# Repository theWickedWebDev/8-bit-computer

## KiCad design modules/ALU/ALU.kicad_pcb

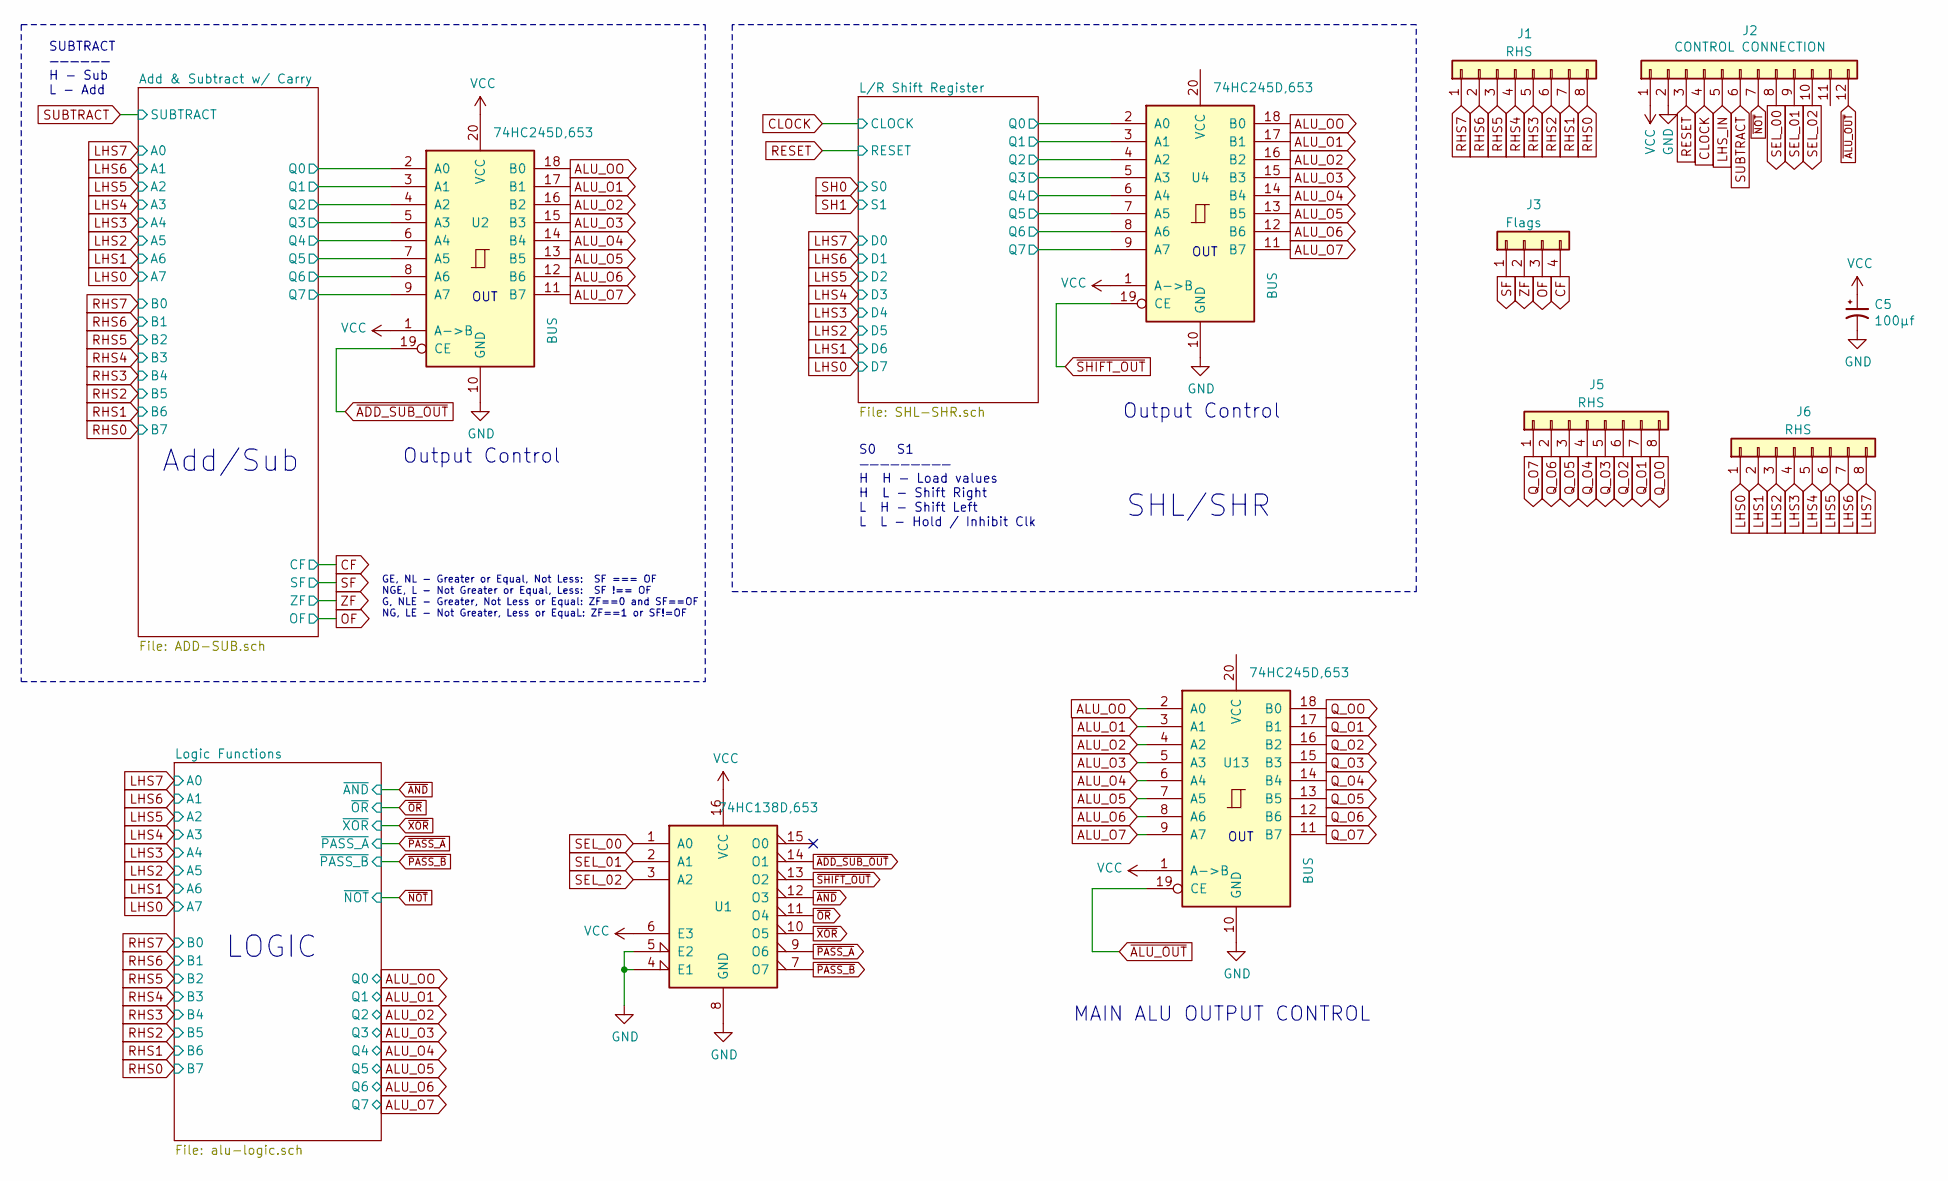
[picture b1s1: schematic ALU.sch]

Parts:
C5: SMD-ECAP-5x5.8; CP_Elec_5x5.8; JLCPCB C140924
J1, J5, J6: Conn_01x08; PinHeader_1x08_P2.54mm_Vertical
J2: Conn_01x12; PinHeader_1x12_P2.54mm_Vertical
J3: Conn_01x04; PinHeader_1x04_P2.54mm_Vertical
U1: 74HC138D,653; SOIC-16_3.9x9.9mm_P1.27mm
U2, U4, U13: 74HC245D,653; SOIC-20W_7.5x12.8mm_P1.27mm

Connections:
/Add & Subtract w/ Carry/Q0: U2.2 (A0); also elsewhere on the board
/Add & Subtract w/ Carry/Q1: U2.3 (A1); also elsewhere on the board
/Add & Subtract w/ Carry/Q2: U2.4 (A2); also elsewhere on the board
/Add & Subtract w/ Carry/Q3: U2.5 (A3); also elsewhere on the board
/Add & Subtract w/ Carry/Q4: U2.6 (A4); also elsewhere on the board
/Add & Subtract w/ Carry/Q5: U2.7 (A5); also elsewhere on the board
/Add & Subtract w/ Carry/Q6: U2.8 (A6); also elsewhere on the board
/Add & Subtract w/ Carry/Q7: U2.9 (A7); also elsewhere on the board
/L/R Shift Register/Q0: U4.2 (A0); also elsewhere on the board
/L/R Shift Register/Q1: U4.3 (A1); also elsewhere on the board
/L/R Shift Register/Q2: U4.4 (A2); also elsewhere on the board
/L/R Shift Register/Q3: U4.5 (A3); also elsewhere on the board
/L/R Shift Register/Q4: U4.6 (A4); also elsewhere on the board
/L/R Shift Register/Q5: U4.7 (A5); also elsewhere on the board
/L/R Shift Register/Q6: U4.8 (A6); also elsewhere on the board
/L/R Shift Register/Q7: U4.9 (A7); also elsewhere on the board
ALU_O1: U2.17 (B1), U4.17 (B1), U13.3 (A1); also elsewhere on the board
ALU_O2: U2.16 (B2), U4.16 (B2), U13.4 (A2); also elsewhere on the board
ALU_O3: U2.15 (B3), U4.15 (B3), U13.5 (A3); also elsewhere on the board
ALU_O4: U2.14 (B4), U4.14 (B4), U13.6 (A4); also elsewhere on the board
ALU_O5: U2.13 (B5), U4.13 (B5), U13.7 (A5); also elsewhere on the board
ALU_O6: U2.12 (B6), U4.12 (B6), U13.8 (A6); also elsewhere on the board
ALU_O7: U2.11 (B7), U4.11 (B7), U13.9 (A7); also elsewhere on the board
ALU_OO: U2.18 (B0), U4.18 (B0), U13.2 (A0); also elsewhere on the board
CF: J3.4; also elsewhere on the board
CLOCK: J2.4; also elsewhere on the board
GND: C5.2, J2.2, U1.4 (E1), U1.5 (E2), U1.8 (GND), U2.10 (GND), U4.10 (GND), U13.10 (GND); also elsewhere on the board
LHS0: J6.1; also elsewhere on the board
LHS1: J6.2; also elsewhere on the board
LHS2: J6.3; also elsewhere on the board
LHS3: J6.4; also elsewhere on the board
LHS4: J6.5; also elsewhere on the board
LHS5: J6.6; also elsewhere on the board
LHS6: J6.7; also elsewhere on the board
LHS7: J6.8; also elsewhere on the board
LHS_IN: J2.5
OF: J3.3
Q_O1: J5.7, U13.17 (B1)
Q_O2: J5.6, U13.16 (B2)
Q_O3: J5.5, U13.15 (B3)
Q_O4: J5.4, U13.14 (B4)
Q_O5: J5.3, U13.13 (B5)
Q_O6: J5.2, U13.12 (B6)
Q_O7: J5.1, U13.11 (B7)
Q_OO: J5.8, U13.18 (B0)
RESET: J2.3; also elsewhere on the board
RHS0: J1.8; also elsewhere on the board
RHS1: J1.7; also elsewhere on the board
RHS2: J1.6; also elsewhere on the board
RHS3: J1.5; also elsewhere on the board
RHS4: J1.4; also elsewhere on the board
RHS5: J1.3; also elsewhere on the board
RHS6: J1.2; also elsewhere on the board
RHS7: J1.1; also elsewhere on the board
SEL_00: J2.8, U1.1 (A0)
SEL_01: J2.9, U1.2 (A1)
SEL_02: J2.10, U1.3 (A2)
SF: J3.1; also elsewhere on the board
SUBTRACT: J2.6; also elsewhere on the board
VCC: C5.1, J2.1, U1.6 (E3), U1.16 (VCC), U2.1 (A->B), U2.20 (VCC), U4.1 (A->B), U13.1 (A->B); also elsewhere on the board
ZF: J3.2; also elsewhere on the board
~ADD_SUB_OUT: U1.14 (O1), U2.19 (CE)
~ALU_OUT: J2.12, U13.19 (CE)
~AND: U1.12 (O3); also elsewhere on the board
~NOT: J2.7; also elsewhere on the board
~OR: U1.11 (O4); also elsewhere on the board
~PASS_A: U1.9 (O6); also elsewhere on the board
~PASS_B: U1.7 (O7); also elsewhere on the board
~SHIFT_OUT: U1.13 (O2), U4.19 (CE)
~XOR: U1.10 (O5); also elsewhere on the board

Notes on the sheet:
OUT
Add/Sub
Output Control
S0 S1 ————————— H H - Load values H L - Shift Right L H - Shift Left L L - Hold / Inhibit Clk
SHL/SHR
SUBTRACT —————— H - Sub L - Add
GE, NL - Greater or Equal, Not Less: SF === OF NGE, L - Not Greater or Equal, Less: SF !== OF G, NLE - Greater, Not Less or Equal: ZF==0 and SF==OF NG, LE - Not Greater, Less or EquaL: ZF==1 or SF!=OF
LOGIC
MAIN ALU OUTPUT CONTROL

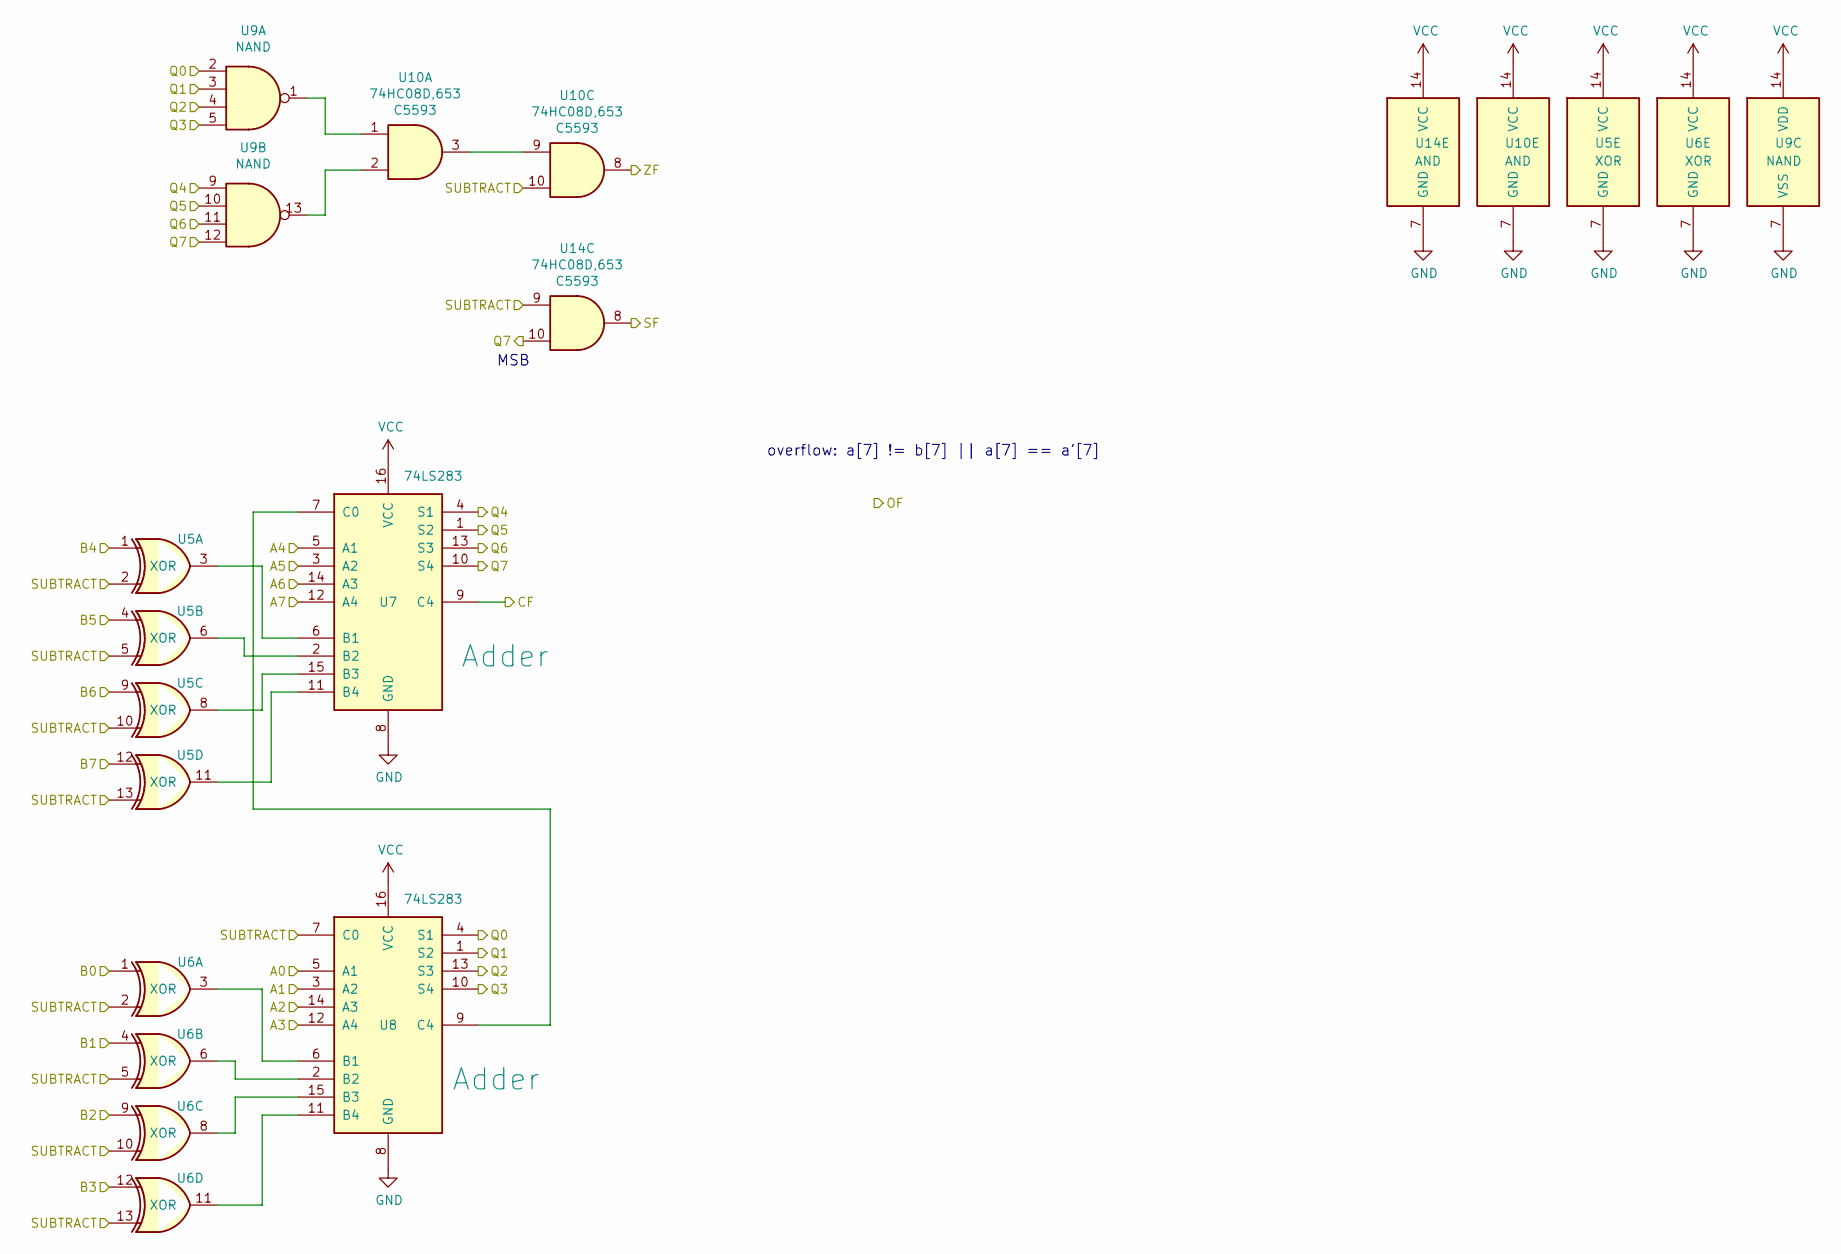
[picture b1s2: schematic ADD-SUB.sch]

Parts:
U5, U6: MM74HC86MX; SOIC-14_3.9x8.7mm_P1.27mm
U7, U8: 74LS283; DIP-16_W7.62mm
U9: CD4012BM; SOIC-14_3.9x8.7mm_P1.27mm
U10, U14: 74HC08D,653; SOIC-14_3.9x8.7mm_P1.27mm

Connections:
/Add & Subtract w/ Carry/Q0: U8.4 (S1), U9.2; also elsewhere on the board
/Add & Subtract w/ Carry/Q1: U8.1 (S2), U9.3; also elsewhere on the board
/Add & Subtract w/ Carry/Q2: U8.13 (S3), U9.4; also elsewhere on the board
/Add & Subtract w/ Carry/Q3: U8.10 (S4), U9.5; also elsewhere on the board
/Add & Subtract w/ Carry/Q4: U7.4 (S1), U9.9; also elsewhere on the board
/Add & Subtract w/ Carry/Q5: U7.1 (S2), U9.10; also elsewhere on the board
/Add & Subtract w/ Carry/Q6: U7.13 (S3), U9.11; also elsewhere on the board
/Add & Subtract w/ Carry/Q7: U7.10 (S4), U9.12, U14.10; also elsewhere on the board
CF: U7.9 (C4); also elsewhere on the board
GND: U5.7 (GND), U6.7 (GND), U7.8 (GND), U8.8 (GND), U9.7 (VSS), U10.7 (GND), U14.7 (GND); also elsewhere on the board
LHS0: U7.12 (A4); also elsewhere on the board
LHS1: U7.14 (A3); also elsewhere on the board
LHS2: U7.3 (A2); also elsewhere on the board
LHS3: U7.5 (A1); also elsewhere on the board
LHS4: U8.12 (A4); also elsewhere on the board
LHS5: U8.14 (A3); also elsewhere on the board
LHS6: U8.3 (A2); also elsewhere on the board
LHS7: U8.5 (A1); also elsewhere on the board
unnamed: U5.3, U7.6 (B1)
unnamed: U5.6, U7.2 (B2)
unnamed: U5.8, U7.15 (B3)
unnamed: U5.11, U7.11 (B4)
unnamed: U6.3, U8.6 (B1)
unnamed: U6.6, U8.2 (B2)
unnamed: U6.8, U8.15 (B3)
unnamed: U6.11, U8.11 (B4)
unnamed: U7.7 (C0), U8.9 (C4)
unnamed: U9.1, U10.1
unnamed: U9.13, U10.2
unnamed: U10.3, U10.9
RHS0: U5.12; also elsewhere on the board
RHS1: U5.9; also elsewhere on the board
RHS2: U5.4; also elsewhere on the board
RHS3: U5.1; also elsewhere on the board
RHS4: U6.12; also elsewhere on the board
RHS5: U6.9; also elsewhere on the board
RHS6: U6.4; also elsewhere on the board
RHS7: U6.1; also elsewhere on the board
SF: U14.8; also elsewhere on the board
SUBTRACT: U5.2, U5.5, U5.10, U5.13, U6.2, U6.5, U6.10, U6.13, U8.7 (C0), U10.10, U14.9; also elsewhere on the board
VCC: U5.14 (VCC), U6.14 (VCC), U7.16 (VCC), U8.16 (VCC), U9.14 (VDD), U10.14 (VCC), U14.14 (VCC); also elsewhere on the board
ZF: U10.8; also elsewhere on the board

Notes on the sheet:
MSB
overflow: a[7] != b[7] || a[7] == a'[7]

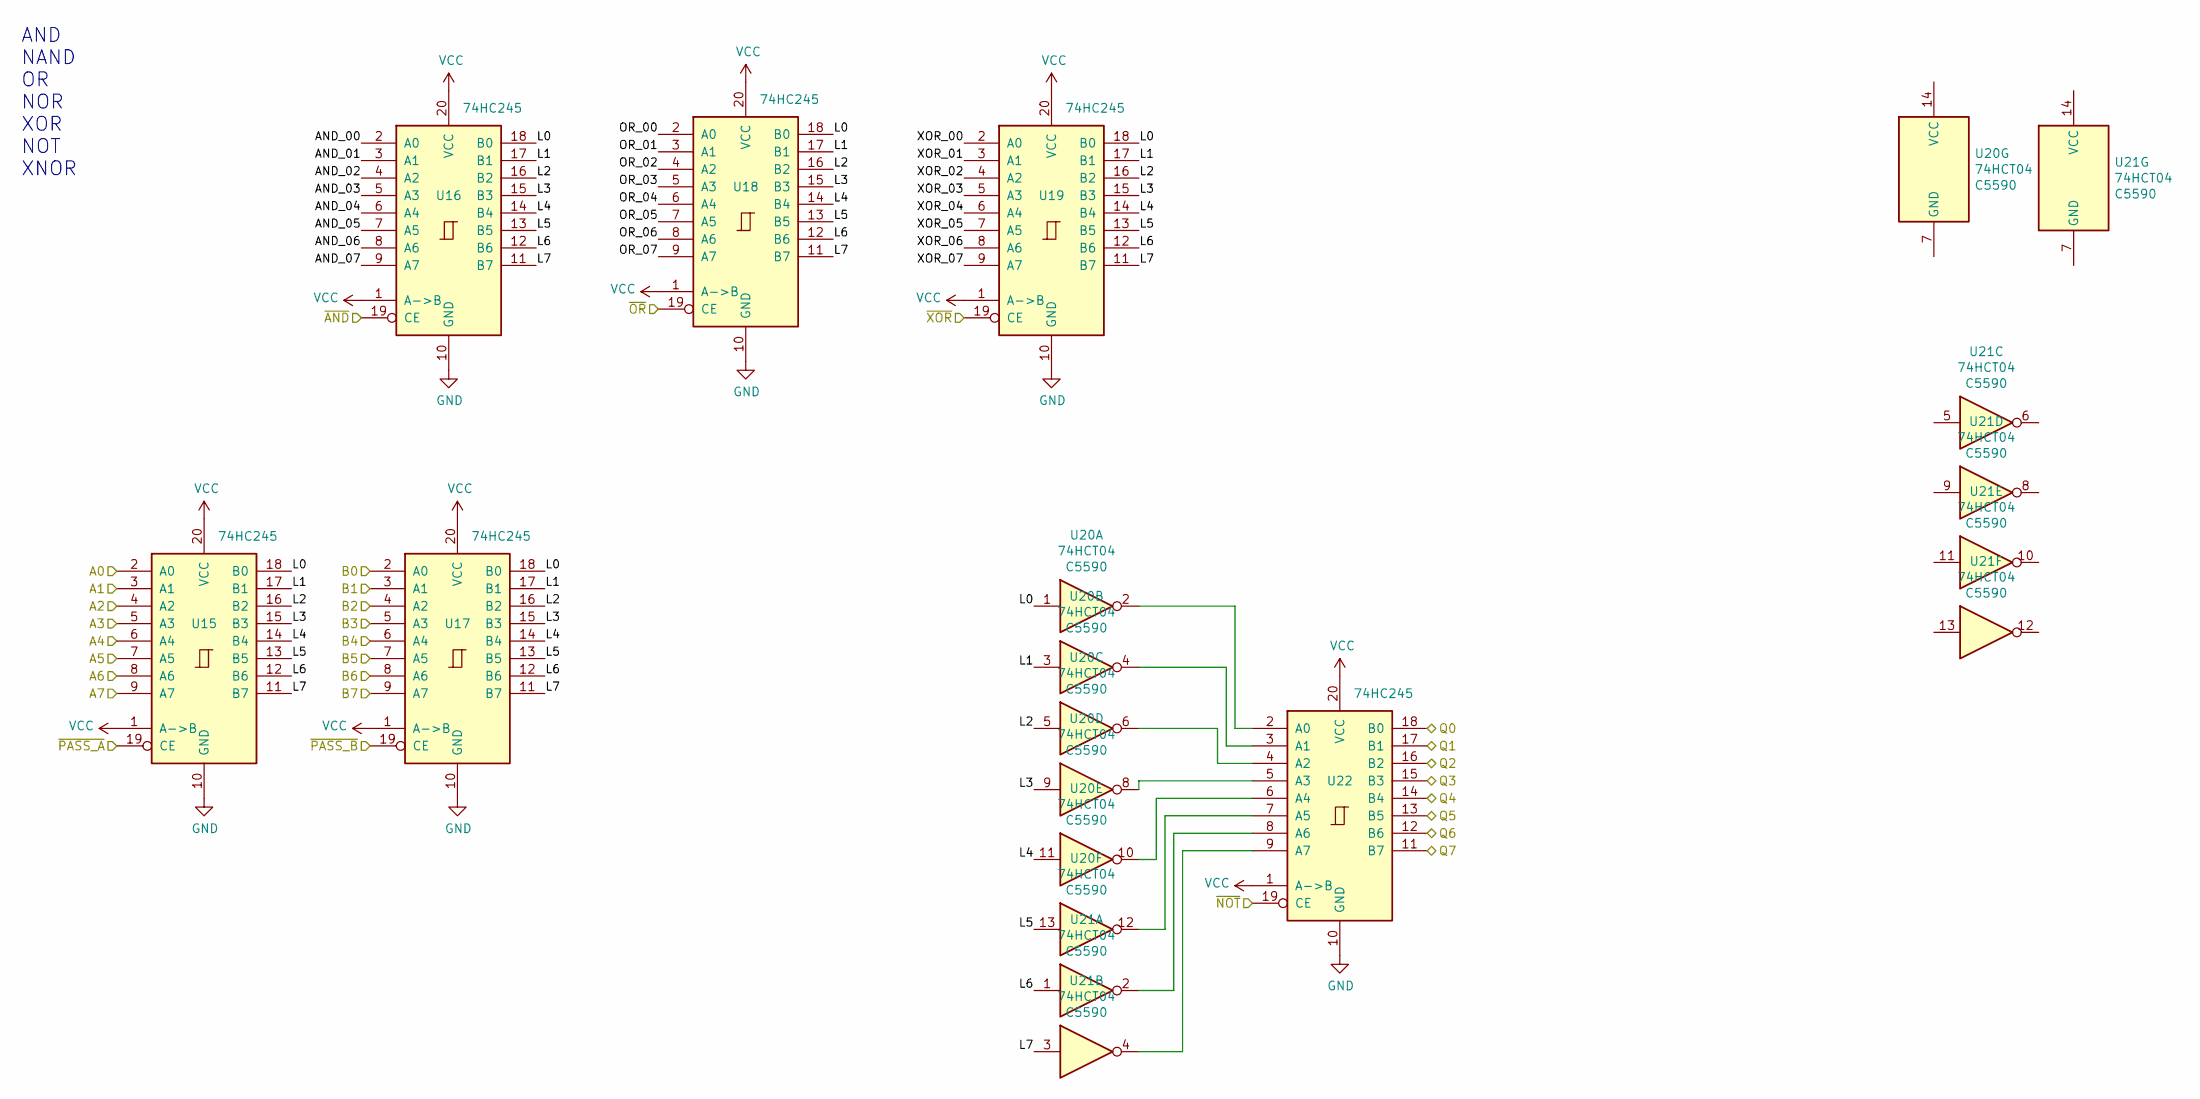
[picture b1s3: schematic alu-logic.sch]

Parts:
U15, U16, U17, U18, U19, U22: 74HC245; SOIC-20W_7.5x12.8mm_P1.27mm
U20, U21: 74HCT04; SOIC-14_3.9x8.7mm_P1.27mm

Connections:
/Logic Functions/AND_00: U16.2 (A0)
/Logic Functions/AND_01: U16.3 (A1)
/Logic Functions/AND_02: U16.4 (A2)
/Logic Functions/AND_03: U16.5 (A3)
/Logic Functions/AND_04: U16.6 (A4)
/Logic Functions/AND_05: U16.7 (A5)
/Logic Functions/AND_06: U16.8 (A6)
/Logic Functions/AND_07: U16.9 (A7)
/Logic Functions/L0: U15.18 (B0), U16.18 (B0), U17.18 (B0), U18.18 (B0), U19.18 (B0), U20.1
/Logic Functions/L1: U15.17 (B1), U16.17 (B1), U17.17 (B1), U18.17 (B1), U19.17 (B1), U20.3
/Logic Functions/L2: U15.16 (B2), U16.16 (B2), U17.16 (B2), U18.16 (B2), U19.16 (B2), U20.5
/Logic Functions/L3: U15.15 (B3), U16.15 (B3), U17.15 (B3), U18.15 (B3), U19.15 (B3), U20.9
/Logic Functions/L4: U15.14 (B4), U16.14 (B4), U17.14 (B4), U18.14 (B4), U19.14 (B4), U20.11
/Logic Functions/L5: U15.13 (B5), U16.13 (B5), U17.13 (B5), U18.13 (B5), U19.13 (B5), U20.13
/Logic Functions/L6: U15.12 (B6), U16.12 (B6), U17.12 (B6), U18.12 (B6), U19.12 (B6), U21.1
/Logic Functions/L7: U15.11 (B7), U16.11 (B7), U17.11 (B7), U18.11 (B7), U19.11 (B7), U21.3
/Logic Functions/OR_00: U18.2 (A0)
/Logic Functions/OR_01: U18.3 (A1)
/Logic Functions/OR_02: U18.4 (A2)
/Logic Functions/OR_03: U18.5 (A3)
/Logic Functions/OR_04: U18.6 (A4)
/Logic Functions/OR_05: U18.7 (A5)
/Logic Functions/OR_06: U18.8 (A6)
/Logic Functions/OR_07: U18.9 (A7)
/Logic Functions/XOR_00: U19.2 (A0)
/Logic Functions/XOR_01: U19.3 (A1)
/Logic Functions/XOR_02: U19.4 (A2)
/Logic Functions/XOR_03: U19.5 (A3)
/Logic Functions/XOR_04: U19.6 (A4)
/Logic Functions/XOR_05: U19.7 (A5)
/Logic Functions/XOR_06: U19.8 (A6)
/Logic Functions/XOR_07: U19.9 (A7)
ALU_O1: U22.17 (B1); also elsewhere on the board
ALU_O2: U22.16 (B2); also elsewhere on the board
ALU_O3: U22.15 (B3); also elsewhere on the board
ALU_O4: U22.14 (B4); also elsewhere on the board
ALU_O5: U22.13 (B5); also elsewhere on the board
ALU_O6: U22.12 (B6); also elsewhere on the board
ALU_O7: U22.11 (B7); also elsewhere on the board
ALU_OO: U22.18 (B0); also elsewhere on the board
GND: U15.10 (GND), U16.10 (GND), U17.10 (GND), U18.10 (GND), U19.10 (GND), U22.10 (GND); also elsewhere on the board
LHS0: U15.9 (A7); also elsewhere on the board
LHS1: U15.8 (A6); also elsewhere on the board
LHS2: U15.7 (A5); also elsewhere on the board
LHS3: U15.6 (A4); also elsewhere on the board
LHS4: U15.5 (A3); also elsewhere on the board
LHS5: U15.4 (A2); also elsewhere on the board
LHS6: U15.3 (A1); also elsewhere on the board
LHS7: U15.2 (A0); also elsewhere on the board
unnamed: U20.2, U22.2 (A0)
unnamed: U20.4, U22.3 (A1)
unnamed: U20.6, U22.4 (A2)
unnamed: U20.8, U22.5 (A3)
unnamed: U20.10, U22.6 (A4)
unnamed: U20.12, U22.7 (A5)
unnamed: U21.2, U22.8 (A6)
unnamed: U21.4, U22.9 (A7)
RHS0: U17.9 (A7); also elsewhere on the board
RHS1: U17.8 (A6); also elsewhere on the board
RHS2: U17.7 (A5); also elsewhere on the board
RHS3: U17.6 (A4); also elsewhere on the board
RHS4: U17.5 (A3); also elsewhere on the board
RHS5: U17.4 (A2); also elsewhere on the board
RHS6: U17.3 (A1); also elsewhere on the board
RHS7: U17.2 (A0); also elsewhere on the board
VCC: U15.1 (A->B), U15.20 (VCC), U16.1 (A->B), U16.20 (VCC), U17.1 (A->B), U17.20 (VCC), U18.1 (A->B), U18.20 (VCC), U19.1 (A->B), U19.20 (VCC), U22.1 (A->B), U22.20 (VCC); also elsewhere on the board
~AND: U16.19 (CE); also elsewhere on the board
~NOT: U22.19 (CE); also elsewhere on the board
~OR: U18.19 (CE); also elsewhere on the board
~PASS_A: U15.19 (CE); also elsewhere on the board
~PASS_B: U17.19 (CE); also elsewhere on the board
~XOR: U19.19 (CE); also elsewhere on the board

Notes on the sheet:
AND NAND OR NOR XOR NOT XNOR

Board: 2 copper layers, 28 parts (0 on the bottom side), 98 nets, no tracks yet.

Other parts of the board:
C1: CL05A106MQ5NUNC; C_0402_1005Metric
U11, U12: 74HC194D,653; SOIC-16_3.9x9.9mm_P1.27mm

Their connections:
/L/R Shift Register/Q0: U11.15; also elsewhere on the board
/L/R Shift Register/Q1: U11.14; also elsewhere on the board
/L/R Shift Register/Q2: U11.13; also elsewhere on the board
/L/R Shift Register/Q3: U11.12, U12.2; also elsewhere on the board
/L/R Shift Register/Q4: U11.7, U12.15; also elsewhere on the board
/L/R Shift Register/Q5: U12.14; also elsewhere on the board
/L/R Shift Register/Q6: U12.13; also elsewhere on the board
/L/R Shift Register/Q7: U12.12; also elsewhere on the board
CLOCK: U11.11, U12.11; also elsewhere on the board
GND: C1.2, U11.2, U11.8, U12.7, U12.8; also elsewhere on the board
LHS0: U12.6; also elsewhere on the board
LHS1: U12.5; also elsewhere on the board
LHS2: U12.4; also elsewhere on the board
LHS3: U12.3; also elsewhere on the board
LHS4: U11.6; also elsewhere on the board
LHS5: U11.5; also elsewhere on the board
LHS6: U11.4; also elsewhere on the board
LHS7: U11.3; also elsewhere on the board
RESET: U11.1, U12.1; also elsewhere on the board
SH0: U11.9, U12.9
SH1: U11.10, U12.10
VCC: C1.1, U11.16, U12.16; also elsewhere on the board

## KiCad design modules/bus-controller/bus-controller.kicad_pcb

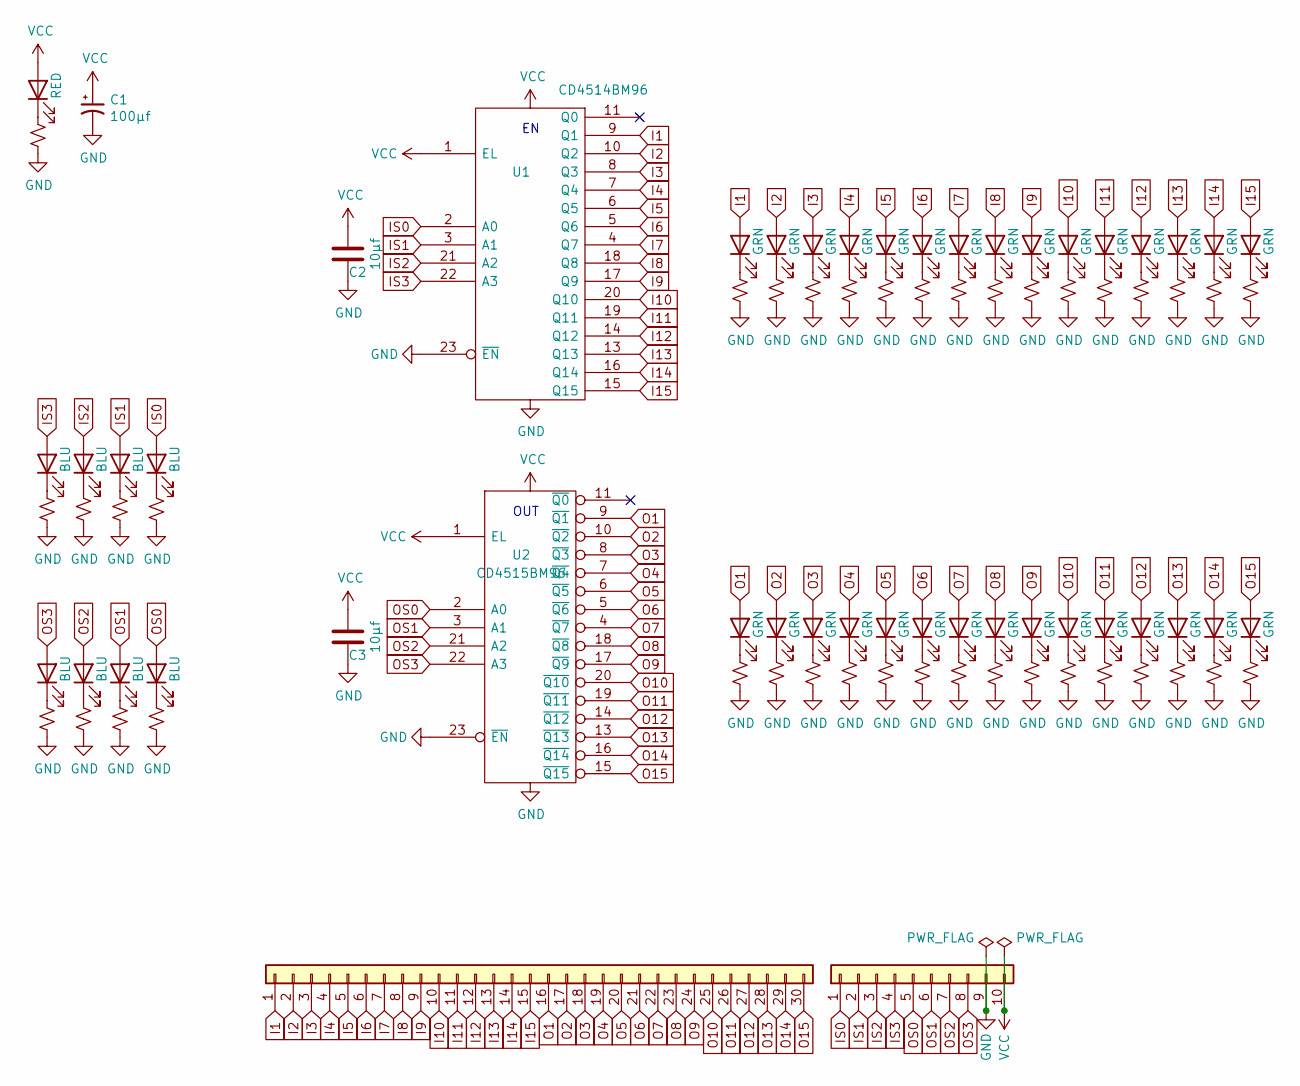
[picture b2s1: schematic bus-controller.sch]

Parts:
C1: SMD-ECAP-5x5.8; CP_Elec_5x5.8; JLCPCB C140924
C2, C3: CL05A106MQ5NUNC; C_0402_1005Metric; JLCPCB C15525
D1, D2, D3, D4, D5, D6, D7, D8: 19-217/BHC-ZL1M2RY/3T; LED_0603_1608Metric; JLCPCB C72041
D9, D10, D11, D12, D13, D14, D15, D16, D17, D18, D19, D20, D21, D22, D23, D24, D25, D26, D27, D28, D29, D30, D31, D32, D33, D34, D35, D36, D37, D38: 19-217/GHC-YR1S2/3T; LED_0603_1608Metric; JLCPCB C72043
D39: NCD0805R1; LED_0805_2012Metric; JLCPCB C84256
J1: Conn_01x30; PinHeader_1x30_P2.54mm_Vertical
J2: Conn_01x10; PinHeader_1x10_P2.54mm_Vertical
R1, R2, R3, R4, R5, R6, R7, R8, R9, R10, R11, R12, R13, R14, R15, R16, R17, R18, R19, R20, R21, R22, R23, R24, R25, R26, R27, R28, R29, R30, R31, R32, R33, R34, R35, R36, R37, R38, R39: 0402WGF1001TCE; R_0402_1005Metric; JLCPCB C11702
U1: CD4514BM96; SOIC-24W_7.5x15.4mm_P1.27mm; JLCPCB C496122
U2: CD4515BM96; SOIC-24W_7.5x15.4mm_P1.27mm; JLCPCB C368608

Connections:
GND: C1.2, C2.2, C3.2, J2.9, R1.2, R2.2, R3.2, R4.2, R5.2, R6.2, R7.2, R8.2, R9.2, R10.2, R11.2, R12.2, R13.2, R14.2, R15.2, R16.2, R17.2, R18.2, R19.2, R20.2, R21.2, R22.2, R23.2, R24.2, R25.2, R26.2, R27.2, R28.2, R29.2, R30.2, R31.2, R32.2, R33.2, R34.2, R35.2, R36.2, R37.2, R38.2, R39.2, U1.12 (Vss), U1.23 (~EN), U2.12 (Vss), U2.23 (~EN)
I1: D9.2 (A), J1.1, U1.9 (Q1)
I2: D10.2 (A), J1.2, U1.10 (Q2)
I3: D11.2 (A), J1.3, U1.8 (Q3)
I4: D12.2 (A), J1.4, U1.7 (Q4)
I5: D13.2 (A), J1.5, U1.6 (Q5)
I6: D14.2 (A), J1.6, U1.5 (Q6)
I7: D15.2 (A), J1.7, U1.4 (Q7)
I8: D16.2 (A), J1.8, U1.18 (Q8)
I9: D17.2 (A), J1.9, U1.17 (Q9)
I10: D18.2 (A), J1.10, U1.20 (Q10)
I11: D19.2 (A), J1.11, U1.19 (Q11)
I12: D20.2 (A), J1.12, U1.14 (Q12)
I13: D21.2 (A), J1.13, U1.13 (Q13)
I14: D22.2 (A), J1.14, U1.16 (Q14)
I15: D23.2 (A), J1.15, U1.15 (Q15)
IS0: D7.2 (A), J2.1, U1.2 (A0)
IS1: D5.2 (A), J2.2, U1.3 (A1)
IS2: D3.2 (A), J2.3, U1.21 (A2)
IS3: D1.2 (A), J2.4, U1.22 (A3)
unnamed: D1.1 (K), R1.1
unnamed: D2.1 (K), R2.1
unnamed: D3.1 (K), R3.1
unnamed: D4.1 (K), R4.1
unnamed: D5.1 (K), R5.1
unnamed: D6.1 (K), R6.1
unnamed: D7.1 (K), R7.1
unnamed: D8.1 (K), R8.1
unnamed: D9.1 (K), R9.1
unnamed: D10.1 (K), R10.1
unnamed: D11.1 (K), R11.1
unnamed: D12.1 (K), R12.1
unnamed: D13.1 (K), R13.1
unnamed: D14.1 (K), R14.1
unnamed: D15.1 (K), R15.1
unnamed: D16.1 (K), R16.1
unnamed: D17.1 (K), R17.1
unnamed: D18.1 (K), R18.1
unnamed: D19.1 (K), R19.1
unnamed: D20.1 (K), R20.1
unnamed: D21.1 (K), R21.1
unnamed: D22.1 (K), R22.1
unnamed: D23.1 (K), R23.1
unnamed: D24.1 (K), R24.1
unnamed: D25.1 (K), R25.1
unnamed: D26.1 (K), R26.1
unnamed: D27.1 (K), R27.1
unnamed: D28.1 (K), R28.1
unnamed: D29.1 (K), R29.1
unnamed: D30.1 (K), R30.1
unnamed: D31.1 (K), R31.1
unnamed: D32.1 (K), R32.1
unnamed: D33.1 (K), R33.1
unnamed: D34.1 (K), R34.1
unnamed: D35.1 (K), R35.1
unnamed: D36.1 (K), R36.1
unnamed: D37.1 (K), R37.1
unnamed: D38.1 (K), R38.1
unnamed: D39.1 (K), R39.1
O1: D24.2 (A), J1.16, U2.9 (~Q1)
O2: D25.2 (A), J1.17, U2.10 (~Q2)
O3: D26.2 (A), J1.18, U2.8 (~Q3)
O4: D27.2 (A), J1.19, U2.7 (~Q4)
O5: D28.2 (A), J1.20, U2.6 (~Q5)
O6: D29.2 (A), J1.21, U2.5 (~Q6)
O7: D30.2 (A), J1.22, U2.4 (~Q7)
O8: D31.2 (A), J1.23, U2.18 (~Q8)
O9: D32.2 (A), J1.24, U2.17 (~Q9)
O10: D33.2 (A), J1.25, U2.20 (~Q10)
O11: D34.2 (A), J1.26, U2.19 (~Q11)
O12: D35.2 (A), J1.27, U2.14 (~Q12)
O13: D36.2 (A), J1.28, U2.13 (~Q13)
O14: D37.2 (A), J1.29, U2.16 (~Q14)
O15: D38.2 (A), J1.30, U2.15 (~Q15)
OS0: D8.2 (A), J2.5, U2.2 (A0)
OS1: D6.2 (A), J2.6, U2.3 (A1)
OS2: D4.2 (A), J2.7, U2.21 (A2)
OS3: D2.2 (A), J2.8, U2.22 (A3)
VCC: C1.1, C2.1, C3.1, D39.2 (A), J2.10, U1.1 (EL), U1.24 (Vdd), U2.1 (EL), U2.24 (Vdd)

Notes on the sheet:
OUT

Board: 2 copper layers, 85 parts (2 on the bottom side), 79 nets, no tracks yet.

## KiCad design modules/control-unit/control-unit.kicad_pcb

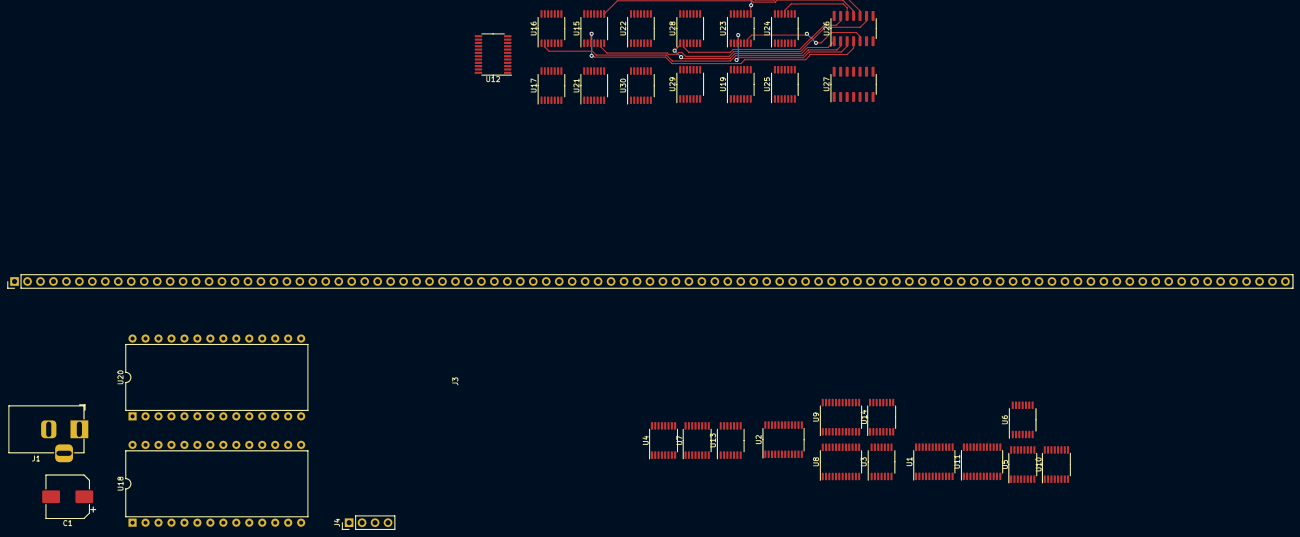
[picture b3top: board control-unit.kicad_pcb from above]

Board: 4 copper layers, 34 parts (0 on the bottom side), 175 nets.

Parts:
C1: CP; CP_Elec_8x10
J1: Barrel_Jack; BarrelJack_Horizontal
J3: Conn_01x99; 1x99_pinheader
J4: Conn_01x04; PinHeader_1x04_P2.54mm_Vertical
U1, U2, U8, U9, U11, U12: 74LS154; TSSOP-24_4.4x7.8mm_P0.65mm
U3, U23, U24, U25: 74LS08; TSSOP-14_4.4x5mm_P0.65mm
U4, U5: 74LS258; TSSOP-16_4.4x5mm_P0.65mm
U6, U13: 74HC04; TSSOP-14_4.4x5mm_P0.65mm
U7, U10: 74LS138; TSSOP-16_4.4x5mm_P0.65mm
U14: 74LS157; TSSOP-16_4.4x5mm_P0.65mm
U15, U17: 74LS00; TSSOP-14_4.4x5mm_P0.65mm
U16, U21: 74LS04; TSSOP-14_4.4x5mm_P0.65mm
U18, U20: 28C256; DIP-28_W15.24mm
U19, U28, U29, U30: 74LS32; TSSOP-14_4.4x5mm_P0.65mm
U22: 74LS86; TSSOP-14_4.4x5mm_P0.65mm
U26, U27: CD4072; SOIC-14_3.9x8.7mm_P1.27mm

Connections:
ALU_CARRY_IN: J3.98, U3.11
ALU_FUNC_0: J3.94, U14.4
ALU_FUNC_1: J3.95, U14.7
ALU_FUNC_2: J3.96, U14.9
ALU_FUNC_3: J3.97, U14.12
ALU_MODE: J3.99, U3.10, U7.12
CARRY_FLAG: J4.4, U3.12, U15.13, U17.2, U19.2, U24.13
EEPROM_0: U1.23, U2.23, U12.23, U14.2, U18.11
EEPROM_1: U1.22, U2.22, U12.22, U14.5, U18.12
EEPROM_2: U1.21, U2.21, U12.21, U14.11, U18.13
EEPROM_3: U1.20, U2.20, U12.20, U14.14, U18.15
EEPROM_4: U7.1, U18.16
EEPROM_5: U7.2, U18.17
EEPROM_6: U7.3, U18.18
EEPROM_7: U7.4, U18.19
EEPROM_8: U8.23, U9.23, U11.23, U20.11
EEPROM_9: U8.22, U9.22, U11.22, U20.12
EEPROM_10: U8.21, U9.21, U11.21, U20.13
EEPROM_11: U8.20, U9.20, U11.20, U20.15
EEPROM_12: U10.1, U20.16
EEPROM_13: U10.2, U20.17
EEPROM_14: U10.3, U20.18
EEPROM_15: U10.4, U20.19
GND: C1.2, J1.2, U1.12, U2.12, U3.7, U4.2, U4.6, U4.8, U4.10, U4.11, U4.13, U4.14, U5.3, U5.6, U5.8, U5.10, U5.11, U5.13, U5.14, U6.7, U7.5, U7.8, U8.12, U9.12, U10.5, U10.8, U11.12, U12.12, U14.3, U14.6, U14.8, U14.10, U14.13, U14.15, U15.7, U16.7, U17.7, U18.14, U18.20, U18.22, U19.7, U20.14, U20.20, U20.22, U21.7, U22.7, U23.7, U24.7, U25.7, U26.7, U27.7, U28.7, U29.7, U30.7
INC_PC: J3.93, U1.11
unnamed: U3.3, U4.15
unnamed: U3.5, U3.8
unnamed: U3.13, U13.2
unnamed: U3.6, U14.1
unnamed: U15.3, U26.4
unnamed: U15.6, U26.9
unnamed: U15.8, U26.11
unnamed: U15.11, U27.2
unnamed: U16.2, U26.2
unnamed: U16.4, U23.1
unnamed: U16.6, U23.4
unnamed: U16.8, U23.9
unnamed: U16.10, U24.12
unnamed: U16.12, U24.1
unnamed: U17.3, U24.5
unnamed: U17.6, U19.5
unnamed: U19.3, U24.2
unnamed: U19.4, U23.11
unnamed: U19.6, U25.2, U25.4
unnamed: U19.8, U27.9
unnamed: U19.9, U22.3, U24.10
unnamed: U19.10, U21.6
unnamed: U21.2, U24.4
unnamed: U21.4, U24.9
unnamed: U21.8, U25.1
unnamed: U21.10, U25.5
unnamed: U21.12, U25.13
unnamed: U23.3, U26.3
unnamed: U23.6, U26.5
unnamed: U23.8, U26.10
unnamed: U24.3, U27.3
unnamed: U24.6, U27.4
unnamed: U24.8, U27.5
unnamed: U24.11, U26.12
unnamed: U25.3, U27.10
unnamed: U25.11, U27.11
unnamed: U25.6, U25.12
unnamed: U26.1, U28.1
unnamed: U26.13, U28.2
unnamed: U27.1, U27.12
unnamed: U27.13, U28.5
unnamed: U28.3, U28.4
OVERFLOW_FLAG: J4.2, U15.2, U17.4, U22.2, U23.2, U23.12
SHA_SEL_00: J3.90, U4.7, U5.7
SHA_SEL_01: J3.89, U4.4, U5.4
SIGN_FLAG: J4.3, U15.5, U17.5, U22.1, U23.5, U23.13
SP_DEC: J3.92, U2.10
SP_INC: J3.91, U2.17
VCC: C1.1, J1.1, U1.24, U2.24, U3.14, U4.3, U4.5, U4.16, U5.2, U5.5, U5.16, U6.14, U7.6, U7.16, U8.24, U9.24, U10.6, U10.16, U11.24, U12.24, U14.16, U15.14, U16.14, U17.14, U18.27, U18.28, U19.14, U20.27, U20.28, U21.14, U22.14, U23.14, U24.14, U25.14, U26.14, U27.14, U28.14, U29.14, U30.14
ZERO_FLAG: J4.1, U15.10, U17.1, U19.1, U21.11, U23.10
~ALU_DATA: J3.34, U9.6
~ALU_FLAG_REG_IN: J3.82, U12.1
~ALU_MODE_0_CARRY_IN_EN: U3.4, U7.10, U13.1
~ALU_MODE_1_EN: U3.9, U7.11
~A_REG_DATA: J3.50, U11.6
~CD_ADDRESS: J3.38, U9.10
~CE_ADDRESS: J3.39, U9.11
~CF_ADDRESS: J3.40, U9.13
~CLEAR_INT_0: J3.83, U2.11
~CLEAR_INT_1: J3.84, U2.13
~CLEAR_INT_2: J3.85, U2.14
~C_DATA: J3.14, U8.2
~C_LSB_DATA: J3.15, U8.3
~C_MSB_DATA: J3.16, U8.4
~DC_ADDRESS: J3.41, U9.14
~DE_ADDRESS: J3.42, U9.15
~DF_ADDRESS: J3.43, U9.16
~D_DATA: J3.17, U8.5
~D_LSB_DATA: J3.18, U8.6
~D_MSB_DATA: J3.19, U8.7
~EC_ADDRESS: J3.44, U9.17
~ED_ADDRESS: J3.45, U11.1
~EF_ADDRESS: J3.46, U11.2
~E_DATA: J3.20, U8.8
~E_LSB_DATA: J3.21, U8.9
~E_MSB_DATA: J3.22, U8.10
~FC_ADDRESS: J3.47, U11.3
~FD_ADDRESS: J3.48, U11.4
~FE_ADDRESS: J3.49, U11.5
~F_DATA: J3.23, U8.11
~F_LSB_DATA: J3.24, U8.13
~F_MSB_DATA: J3.25, U8.14
~HALT: J3.88, U2.16
~INPUT0_DATA: J3.36, U9.8
~INPUT1_DATA: J3.37, U9.9
~IR_ADDRESS: J3.33, U9.5
~JUMP: U12.2, U16.1
~JUMP_JA_JNBE: U12.13, U21.1
~JUMP_JBE_JNA: U12.11, U16.13
~JUMP_JB_JNAE_JC: U12.9, U16.11
~JUMP_JE_JZ: U12.7, U16.9
~JUMP_JGE_JNL: U12.15, U21.9
~JUMP_JG_JNLE: U12.17, U21.13
~JUMP_JLE_JNG: U12.16, U21.5
~JUMP_JL_JNG: U12.14, U21.3
~JUMP_JNB_JAE_JNC: U12.10, U15.12
~JUMP_JNE_JNZ: U12.8, U15.9
~JUMP_JNO: U12.4, U15.1
~JUMP_JNS: U12.6, U15.4
~JUMP_JO: U12.3, U16.3
~JUMP_JS: U12.5, U16.5
~LOAD_A_REGISTER: U2.7, U5.1, U5.15
~LOAD_B_REGISTER: J3.61, U1.2
~LOAD_CODE_SEGMENT: J3.76, U2.1
~LOAD_CONSTANT_REGISTER: J3.66, U1.7
~LOAD_C_REGISTER: J3.62, U1.3
~LOAD_DATA_SEGMENT: J3.77, U2.2
~LOAD_D_REGISTER: J3.63, U1.4
~LOAD_E_REGISTER: J3.64, U1.5
~LOAD_F_REGISTER: J3.65, U1.6
~LOAD_INSTRUCTION_REGISTER: J3.71, U1.13
~LOAD_MAR: J3.72, U1.14
~LOAD_OUTPUT_1: J3.78, U2.3
~LOAD_OUTPUT_2: J3.79, U2.4
~LOAD_PROGRAM_COUNTER_COND: J3.70, U28.6
~LOAD_STACK_POINTER: J3.69, U1.10
~LOAD_SYNTH_1: J3.80, U2.5
~LOAD_SYNTH_2: J3.81, U2.6
~LOAD_TX_LSB_REGISTER: J3.67, U1.8
~LOAD_TX_MSB_REGISTER: J3.68, U1.9
~MEM_DATA: J3.30, U9.2
~PC_ADDRESS: J3.32, U9.4
~READ_MUX0_EN: U8.18, U8.19, U10.15
~READ_MUX1_EN: U9.18, U9.19, U10.14
~READ_MUX2_EN: U10.13, U11.18, U11.19
~READ_UNUSED_1: J3.51, U11.7
~READ_UNUSED_2: J3.52, U11.8
~READ_UNUSED_3: J3.53, U11.9
~READ_UNUSED_4: J3.54, U11.10
~READ_UNUSED_5: J3.55, U11.11
~READ_UNUSED_6: J3.56, U11.13
~READ_UNUSED_7: J3.57, U11.14
~READ_UNUSED_8: J3.58, U11.15
~READ_UNUSED_9: J3.59, U11.16
~READ_UNUSED_10: J3.60, U11.17
~RESET: J3.87, U2.15
~SET_INTERRUPT_FREQ: J3.75, U1.17
~SHIFT_A_LEFT: U2.8, U3.2
~SHIFT_A_RIGHT: U2.9, U3.1, U4.1
~SP_ADDRESS: J3.31, U9.3
~TRANSMIT_UART: J3.74, U1.16
~TX_ADDRESS: J3.28, U8.17
~TX_LSB_DATA: J3.26, U8.15
~TX_MSB_DATA: J3.27, U8.16
~UART_DATA: J3.35, U9.7
~WRITE_MEMORY: J3.73, U1.15
~WRITE_MUX0_EN: U1.18, U1.19, U7.15
~WRITE_MUX1_EN: U2.18, U2.19, U7.14
~WRITE_MUX2_EN: U7.13, U12.18, U12.19
~X_DATA: J3.29, U9.1
